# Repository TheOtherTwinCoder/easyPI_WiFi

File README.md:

# easyPI_WiFi
Simply, a devboard with a WiFi shield using the RPI RM2, made for Macondo!

*Well, what's the point?*

I made easyPI WiFi for one simple reason - its customizability! Most custom board related to the Pi Pico don't have the ability to use shields (especially due to the lack of some pins, like pins 25 and 29) - which isn't great for adding features to your board (from just the regular features of a microcontroller!) 

Features:

- EVERY GPIO pin included with the RP2040 - such as pins 25 and 29 - while not losing out on other pins, like the ADC pins!
- RPI_RM2 compatibility with the shield, allowing for WiFi and Bluetooth
- USB-C rather than the normally used Micro-USB with Picos
- 264 KB of on-chip SRAM
- Software compatible with hundreds of distros and repos (mainly due to RP2040 support)
- All the features of a regular Pi Pico, too!

## How It Works
This'll be added once I build the PCB after reciving my parts!

## BOM
| Reference / Item | Package / Description | Qty | Value / Part | Source / Link | Cost (USD) |
|------------------|----------------------|-----|--------------|---------------|------------|
| C1, C10 | 0402 | 2 | 1uF | https://jlcpcb.com/partdetail/53938-CL05A105KA5NQNC/C52923 | |
| C11, C12, C17, C2, C3, C4, C5, C6, C7, C8, C9 | 0402 | 11 | 0.1uF | https://jlcpcb.com/partdetail/1877-CL05B104KO5NNNC/C1525 | |
| C13, C14 | 0402 | 2 | 10uF | https://jlcpcb.com/partdetail/16204-CL05A106MQ5NUNC/C15525 | |
| C15, C16 | 0402 | 2 | 33pF | https://jlcpcb.com/partdetail/1914-0402CG330J500NT/C1562 | |
| J1 | USB_C_Receptacle_HRO_TYPE-C-31-M-12 | 1 | USB-C Receptacle USB2.0 14P | https://jlcpcb.com/partdetail/Korean_HropartsElec-TYPE_C_31_M12/C165948 | |
| J2, J4 | PinHeader_1x20_P2.54mm_Vertical | 2 | Conn_01x20 | https://jlcpcb.com/partdetail/51993-2_54_1_20PStraightpin/C50981 | |
| J3 | PinHeader_1x03_P2.54mm_Vertical | 1 | 1x3 Header | https://jlcpcb.com/partdetail/25717-1_27_13PPin/C24980 | |
| J5 | PinHeader_1x01_P2.54mm_Vertical | 1 | Conn_01x01 | Not on LCSC | |
| R1, R2 | 0402 | 2 | 5.1kΩ | https://jlcpcb.com/partdetail/26648-0402WGF5101TCE/C25905 | |
| R3, R4 | 0402 | 2 | 27Ω | https://jlcpcb.com/partdetail/1445-RC02K360JT/C1093 | |
| R5, R7 | 0402 | 2 | 1kΩ | https://jlcpcb.com/partdetail/12256-0402WGF1001TCE/C11702 | |
| R6 | 0402 | 1 | 10kΩ | https://jlcpcb.com/partdetail/26274-0402WGJ0103TCE/C25531 | |
| SW1 | Alps SKRK Push Button | 1 | SPST-NO Push Switch | https://www.lcsc.com/product-detail/C2837531.html | |
| U1 | QFN-56-1EP 7x7mm P0.4mm EP3.2x3.2mm | 1 | RP2040 | https://jlcpcb.com/partdetail/LumbergAutomation-2040/C18129058 | |
| U2 | SOT-23 | 1 | MCP1700 Regulator | https://jlcpcb.com/partdetail/MicrochipTech-MCP1700_3302ETO/C511277 | |
| U3 | Winbond USON-8-1EP 3x2mm P0.5mm EP0.2x1.6mm | 1 | W25Q16JVSSIQ Flash Memory | https://jlcpcb.com/partdetail/WinbondElec-W25Q16JVSSIQ/C82317 | |
| Y1 | Crystal_SMD_3225-4Pin 3.2x2.5mm | 1 | 12 MHz Crystal | https://jlcpcb.com/partdetail/NDK-NX3225GA_12MHZ_STD_CRG2/C481407 | |
| LCSC Resistors (10kΩ + 470Ω) | Purchase | 1 | Components | LCSC | 1.55 |
| LCSC Shipping | Shipping | 1 | Shipping | LCSC | 9.01 |
| LCSC Handling Fee | Fee | 1 | Handling | LCSC | 3.00 |
| Amazon Socket Headers | Purchase | 1 | Socket Headers | Amazon | 8.81 |
| PiShop RM2 Module | Purchase | 1 | RM2 Module | PiShop | 4.40 |
| PiShop Shipping | Shipping | 1 | Shipping | PiShop | 6.76 |
| JLCPCB PCBs | Fabrication | 1 | PCB Order | JLCPCB | 5.12 |
| JLCPCB Shipping | Shipping | 1 | Shipping | JLCPCB | 66.03 |
| **TOTAL** |  |  |  |  | **105.13** |

## Images
Schematic for Main PCB:

PCB for Main PCB:

3D View for Main PCB: 

Schematic for WiFi Shield:

PCB for WiFi Shield:

3D View for WiFi Shield:

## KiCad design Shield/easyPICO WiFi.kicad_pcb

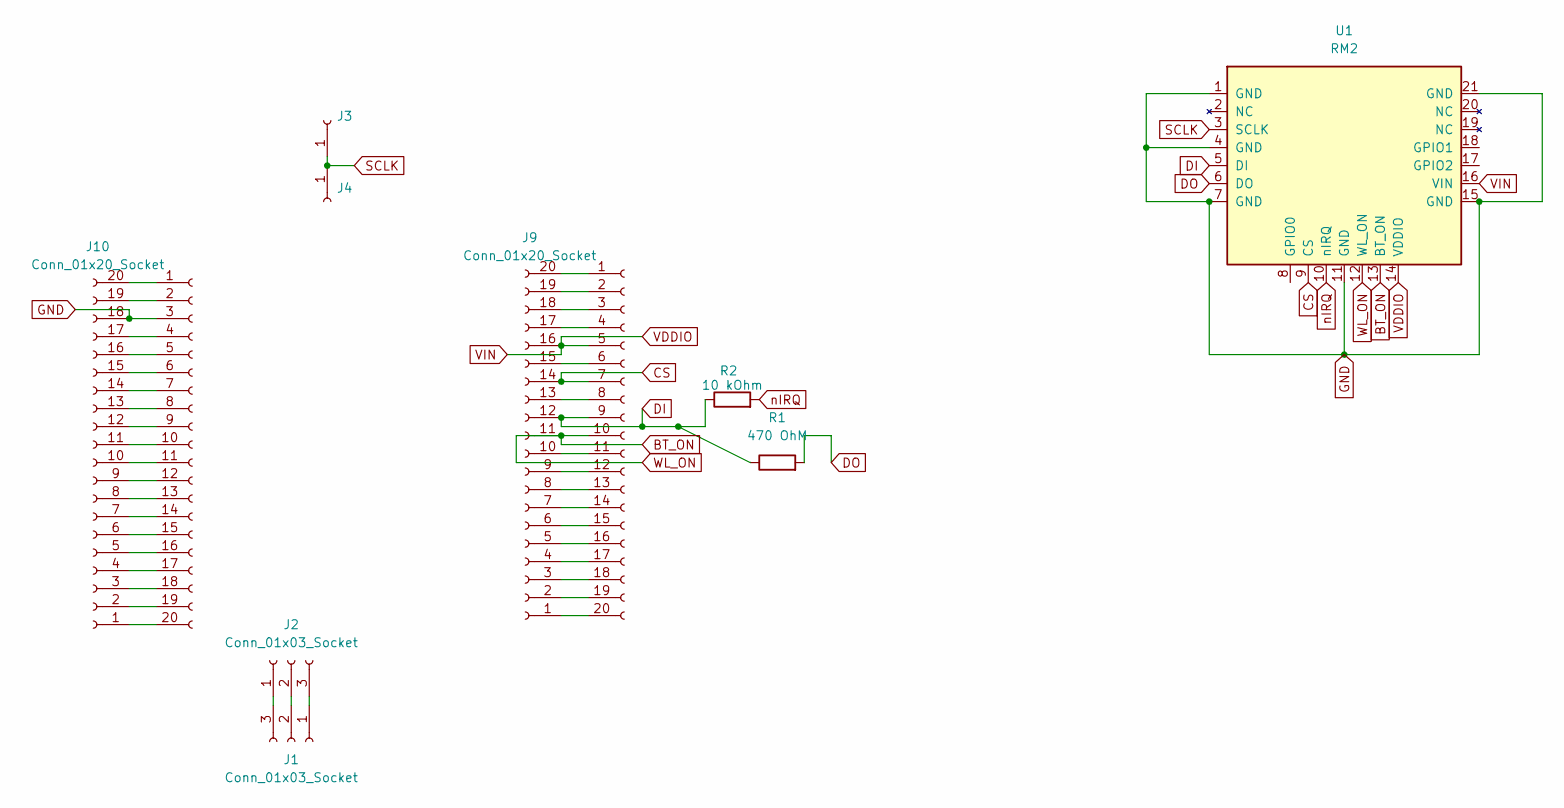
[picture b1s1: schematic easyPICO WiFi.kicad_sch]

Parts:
J1, J2: Conn_01x03_Socket; PinSocket_1x03_P2.54mm_Vertical
J3, J4: Conn_01x01_Socket; PinSocket_1x01_P2.54mm_Vertical
J8, J9, J10, J11: Conn_01x20_Socket; PinSocket_1x20_P2.54mm_Vertical
R1: 470 OhM; R_0805_2012Metric
R2: 10 kOhm; R_0805_2012Metric
U1: RM2; rpi_rmc20452t

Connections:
BT_ON: J8.10, J9.11, U1.12 (WL_ON), U1.13 (BT_ON)
CS: J8.7, J9.14, U1.9 (CS)
DI: J8.9, J9.12, R1.1, R2.1, U1.5 (DI)
DO: R1.2, U1.6 (DO)
GND: J10.18, J11.3, U1.1 (GND), U1.4 (GND), U1.7 (GND), U1.11 (GND), U1.15 (GND), U1.21 (GND)
unnamed: J1.1, J2.3
unnamed: J1.2, J2.2
unnamed: J1.3, J2.1
unnamed: J8.1, J9.20
unnamed: J8.2, J9.19
unnamed: J8.3, J9.18
unnamed: J8.4, J9.17
unnamed: J8.6, J9.15
unnamed: J8.8, J9.13
unnamed: J8.11, J9.10
unnamed: J8.12, J9.9
unnamed: J8.13, J9.8
unnamed: J8.14, J9.7
unnamed: J8.15, J9.6
unnamed: J8.16, J9.5
unnamed: J8.17, J9.4
unnamed: J8.18, J9.3
unnamed: J8.19, J9.2
unnamed: J8.20, J9.1
unnamed: J10.1, J11.20
unnamed: J10.2, J11.19
unnamed: J10.3, J11.18
unnamed: J10.4, J11.17
unnamed: J10.5, J11.16
unnamed: J10.6, J11.15
unnamed: J10.7, J11.14
unnamed: J10.8, J11.13
unnamed: J10.9, J11.12
unnamed: J10.10, J11.11
unnamed: J10.11, J11.10
unnamed: J10.12, J11.9
unnamed: J10.13, J11.8
unnamed: J10.14, J11.7
unnamed: J10.15, J11.6
unnamed: J10.16, J11.5
unnamed: J10.17, J11.4
unnamed: J10.19, J11.2
unnamed: J10.20, J11.1
SCLK: J3.1 (Pin_1_1), J4.1 (Pin_1_1), U1.3 (SCLK)
VDDIO: J8.5, J9.16, U1.14 (VDDIO), U1.16 (VIN)
nIRQ: R2.2, U1.10 (nIRQ)

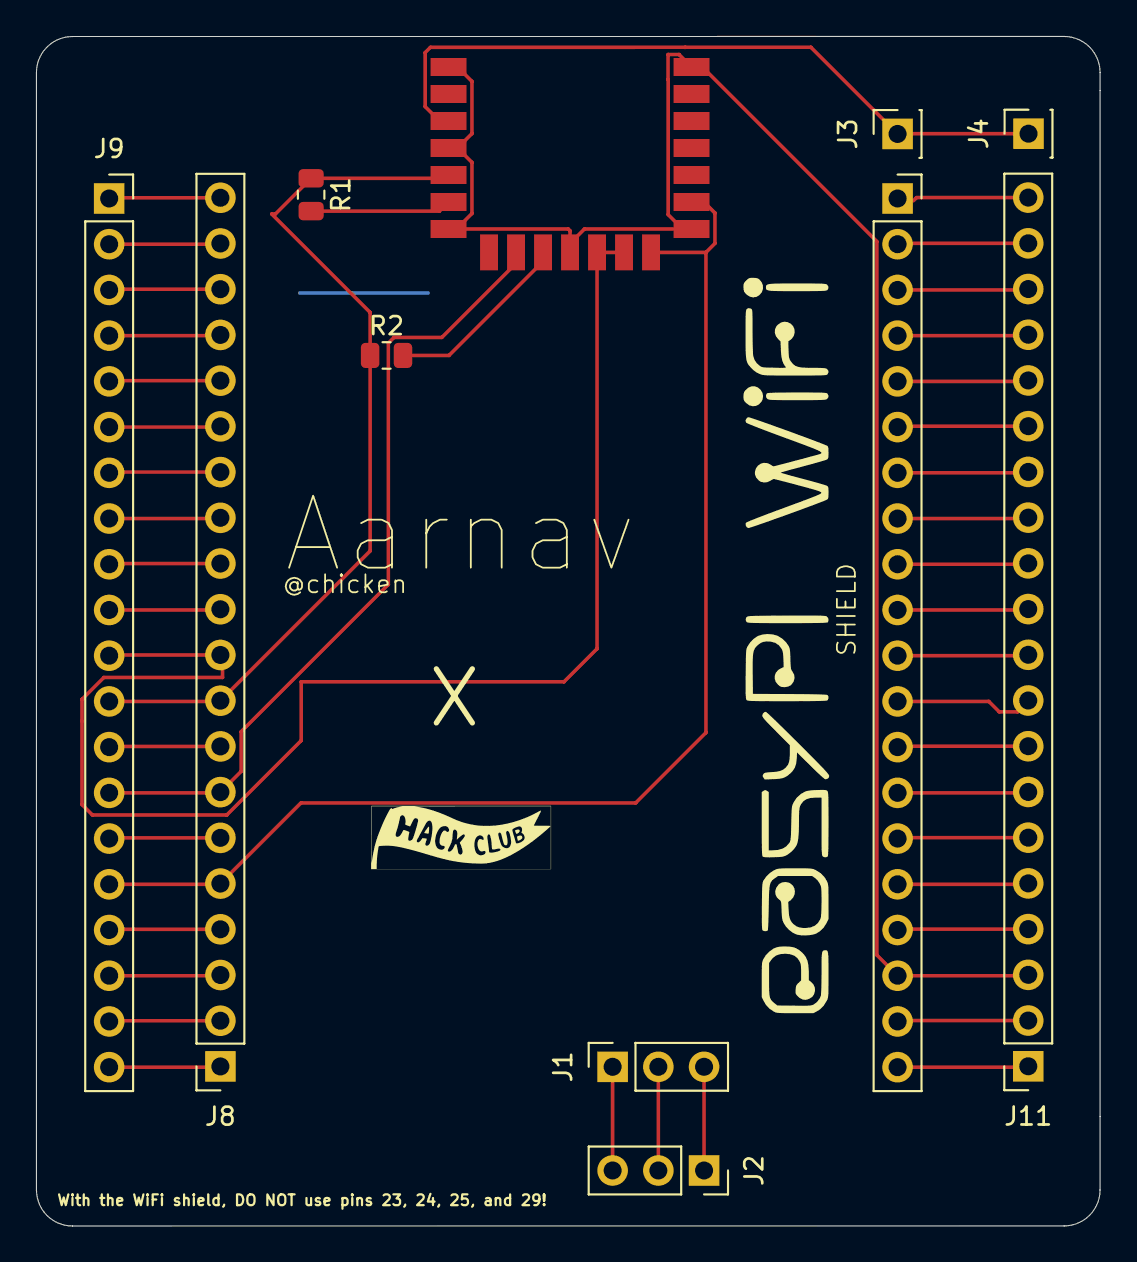
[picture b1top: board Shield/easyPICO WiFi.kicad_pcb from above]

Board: 2 copper layers, 59.1 x 66.1 mm, 11 parts (0 on the bottom side), 46 nets.

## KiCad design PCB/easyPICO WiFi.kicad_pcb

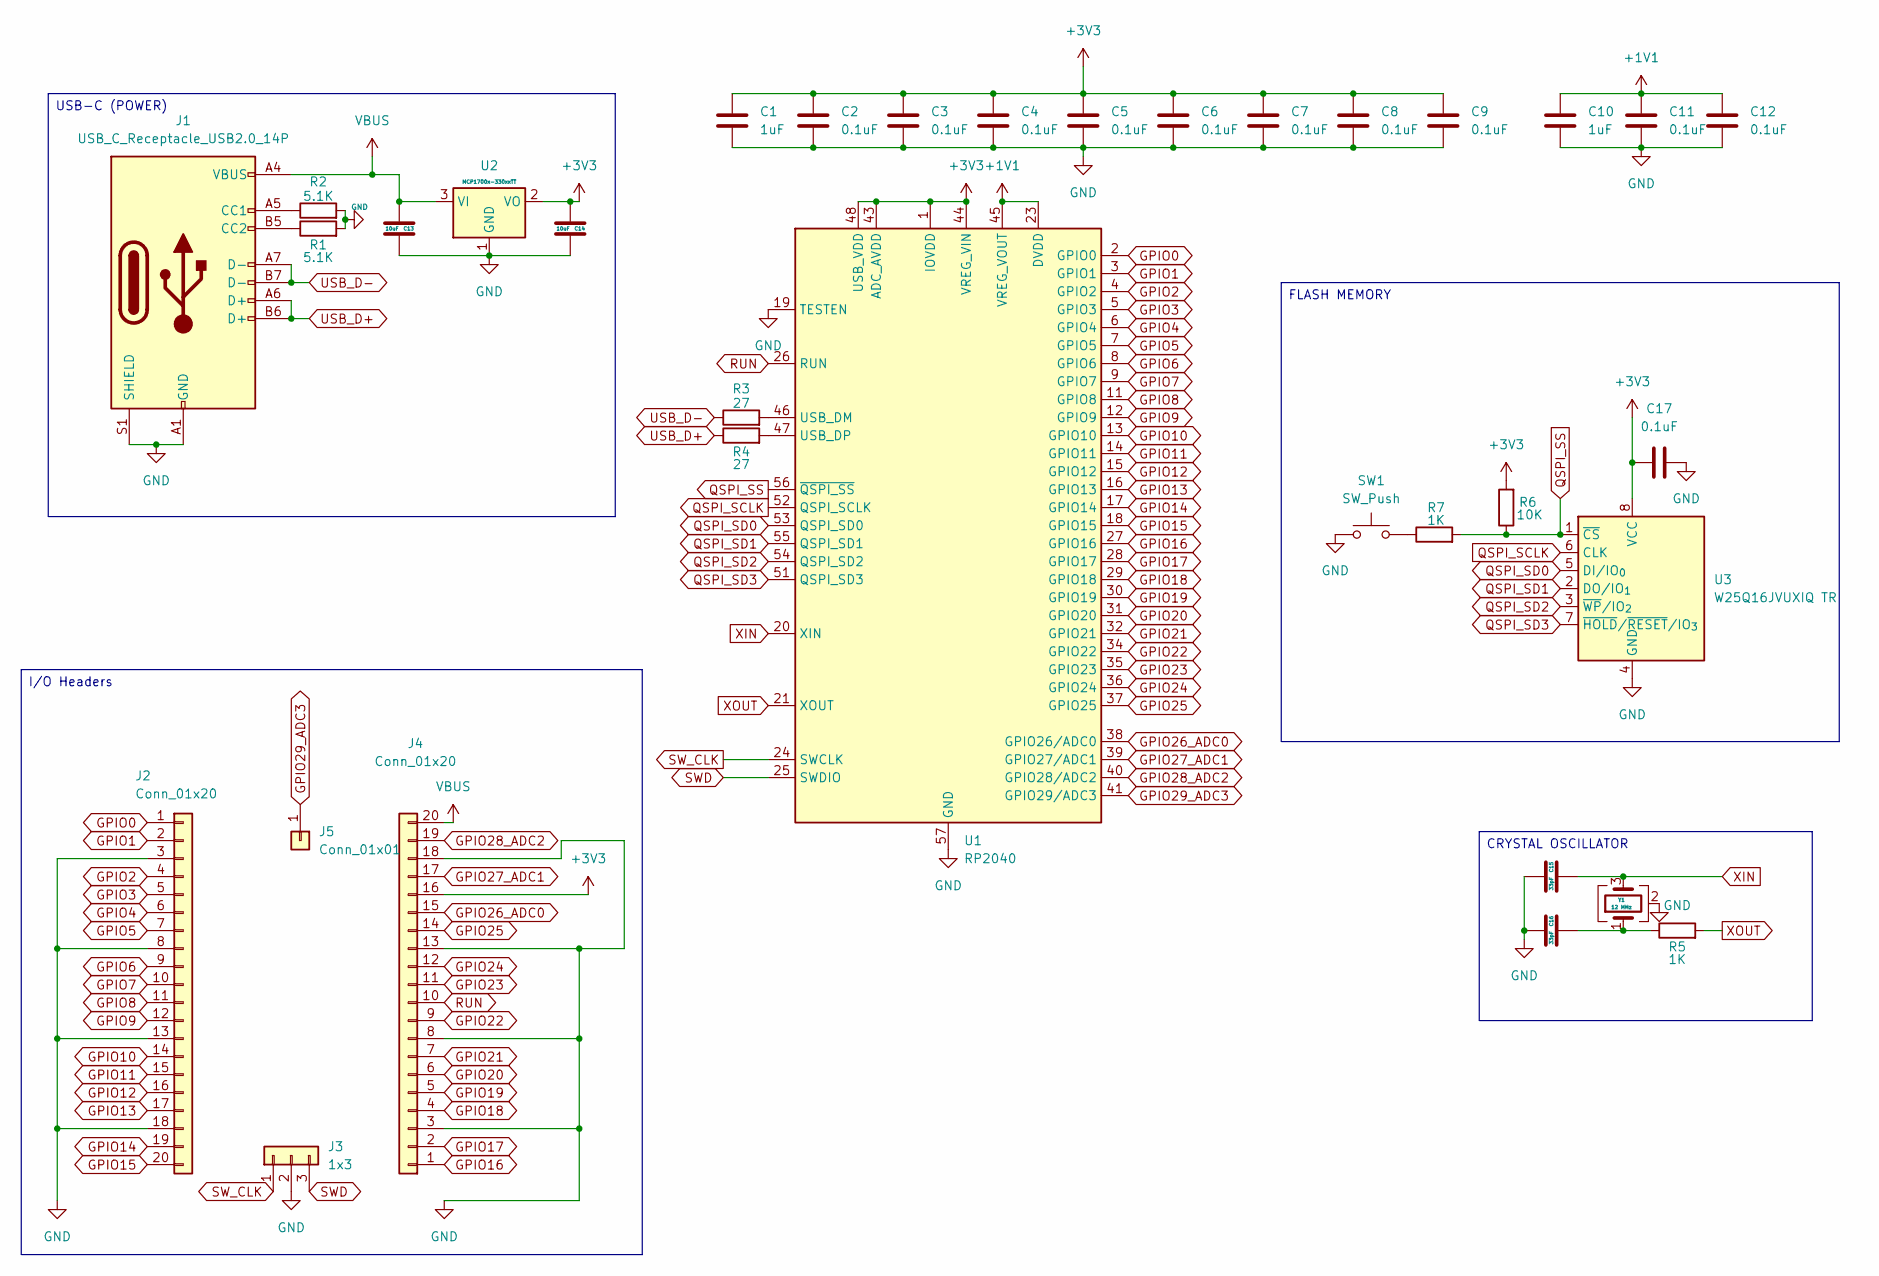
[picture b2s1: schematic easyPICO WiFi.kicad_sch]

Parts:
C1, C10: 1uF; C_0402_1005Metric
C2, C3, C4, C5, C6, C7, C8, C9, C11, C12, C17: 0.1uF; C_0402_1005Metric
C13, C14: 10uF; C_0402_1005Metric
C15, C16: 33pF; C_0402_1005Metric
J1: USB_C_Receptacle_USB2.0_14P; USB_C_Receptacle_HRO_TYPE-C-31-M-12
J2, J4: Conn_01x20; PinHeader_1x20_P2.54mm_Vertical
J3: 1x3; PinHeader_1x03_P2.54mm_Vertical
J5: Conn_01x01; PinHeader_1x01_P2.54mm_Vertical
R1, R2: 5.1K; R_0402_1005Metric
R3, R4: 27; R_0402_1005Metric
R5, R7: 1K; R_0402_1005Metric
R6: 10K; R_0402_1005Metric
SW1: SW_Push; SW_Push_SPST_NO_Alps_SKRK
U1: RP2040; QFN-56-1EP_7x7mm_P0.4mm_EP3.2x3.2mm
U2: MCP1700x-330xxTT; SOT-23
U3: W25Q16JVUXIQ TR; Winbond_USON-8-1EP_3x2mm_P0.5mm_EP0.2x1.6mm
Y1: 12 MHz; Crystal_SMD_3225-4Pin_3.2x2.5mm

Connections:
+1V1: C10.1, C11.1, C12.1, U1.23 (DVDD), U1.45 (VREG_VOUT), U1.50 (DVDD)
+3V3: C1.1, C2.1, C3.1, C4.1, C5.1, C6.1, C7.1, C8.1, C9.1, C14.1, C17.1, J4.16, R6.2, U1.1 (IOVDD), U1.10 (IOVDD), U1.22 (IOVDD), U1.33 (IOVDD), U1.42 (IOVDD), U1.43 (ADC_AVDD), U1.44 (VREG_VIN), U1.48 (USB_VDD), U1.49 (IOVDD), U2.2 (VO), U3.8 (VCC)
GND: C1.2, C2.2, C3.2, C4.2, C5.2, C6.2, C7.2, C8.2, C9.2, C10.2, C11.2, C12.2, C13.2, C14.2, C15.1, C16.1, C17.2, J1.A1 (GND), J1.A12 (GND), J1.B1 (GND), J1.B12 (GND), J1.S1 (SHIELD), J2.3, J2.8, J2.13, J2.18, J3.2, J4.3, J4.8, J4.13, J4.18, R1.2, R2.2, SW1.1, U1.19 (TESTEN), U1.57 (GND), U2.1 (GND), U3.4 (GND), Y1.2 (G), Y1.4 (G)
GPIO0: J2.1, U1.2 (GPIO0)
GPIO1: J2.2, U1.3 (GPIO1)
GPIO2: J2.4, U1.4 (GPIO2)
GPIO3: J2.5, U1.5 (GPIO3)
GPIO4: J2.6, U1.6 (GPIO4)
GPIO5: J2.7, U1.7 (GPIO5)
GPIO6: J2.9, U1.8 (GPIO6)
GPIO7: J2.10, U1.9 (GPIO7)
GPIO8: J2.11, U1.11 (GPIO8)
GPIO9: J2.12, U1.12 (GPIO9)
GPIO10: J2.14, U1.13 (GPIO10)
GPIO11: J2.15, U1.14 (GPIO11)
GPIO12: J2.16, U1.15 (GPIO12)
GPIO13: J2.17, U1.16 (GPIO13)
GPIO14: J2.19, U1.17 (GPIO14)
GPIO15: J2.20, U1.18 (GPIO15)
GPIO16: J4.1, U1.27 (GPIO16)
GPIO17: J4.2, U1.28 (GPIO17)
GPIO18: J4.4, U1.29 (GPIO18)
GPIO19: J4.5, U1.30 (GPIO19)
GPIO20: J4.6, U1.31 (GPIO20)
GPIO21: J4.7, U1.32 (GPIO21)
GPIO22: J4.9, U1.34 (GPIO22)
GPIO23: J4.11, U1.35 (GPIO23)
GPIO24: J4.12, U1.36 (GPIO24)
GPIO25: J4.14, U1.37 (GPIO25)
GPIO26_ADC0: J4.15, U1.38 (GPIO26/ADC0)
GPIO27_ADC1: J4.17, U1.39 (GPIO27/ADC1)
GPIO28_ADC2: J4.19, U1.40 (GPIO28/ADC2)
GPIO29_ADC3: J5.1, U1.41 (GPIO29/ADC3)
unnamed: C16.2, R5.1, Y1.1
unnamed: J1.A5 (CC1), R2.1
unnamed: J1.B5 (CC2), R1.1
unnamed: R7.1, SW1.2
unnamed: R3.2, U1.46 (USB_DM)
unnamed: R4.2, U1.47 (USB_DP)
QSPI_SCLK: U1.52 (QSPI_SCLK), U3.6 (CLK)
QSPI_SD0: U1.53 (QSPI_SD0), U3.5 (DI/IO_{0})
QSPI_SD1: U1.55 (QSPI_SD1), U3.2 (DO/IO_{1})
QSPI_SD2: U1.54 (QSPI_SD2), U3.3 (~WP/IO_{2})
QSPI_SD3: U1.51 (QSPI_SD3), U3.7 (~HOLD/~RESET/IO_{3})
QSPI_SS: R6.1, R7.2, U1.56 (~QSPI_SS), U3.1 (~CS)
RUN: J4.10, U1.26 (RUN)
SWD: J3.3, U1.25 (SWDIO)
SW_CLK: J3.1, U1.24 (SWCLK)
USB_D+: J1.A6 (D+), J1.B6 (D+), R4.1
USB_D-: J1.A7 (D-), J1.B7 (D-), R3.1
VBUS: C13.1, J1.A4 (VBUS), J1.A9 (VBUS), J1.B4 (VBUS), J1.B9 (VBUS), J4.20, U2.3 (VI)
XIN: C15.2, U1.20 (XIN), Y1.3
XOUT: R5.2, U1.21 (XOUT)

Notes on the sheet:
CRYSTAL OSCILLATOR
FLASH MEMORY
USB-C (POWER)
I/O Headers

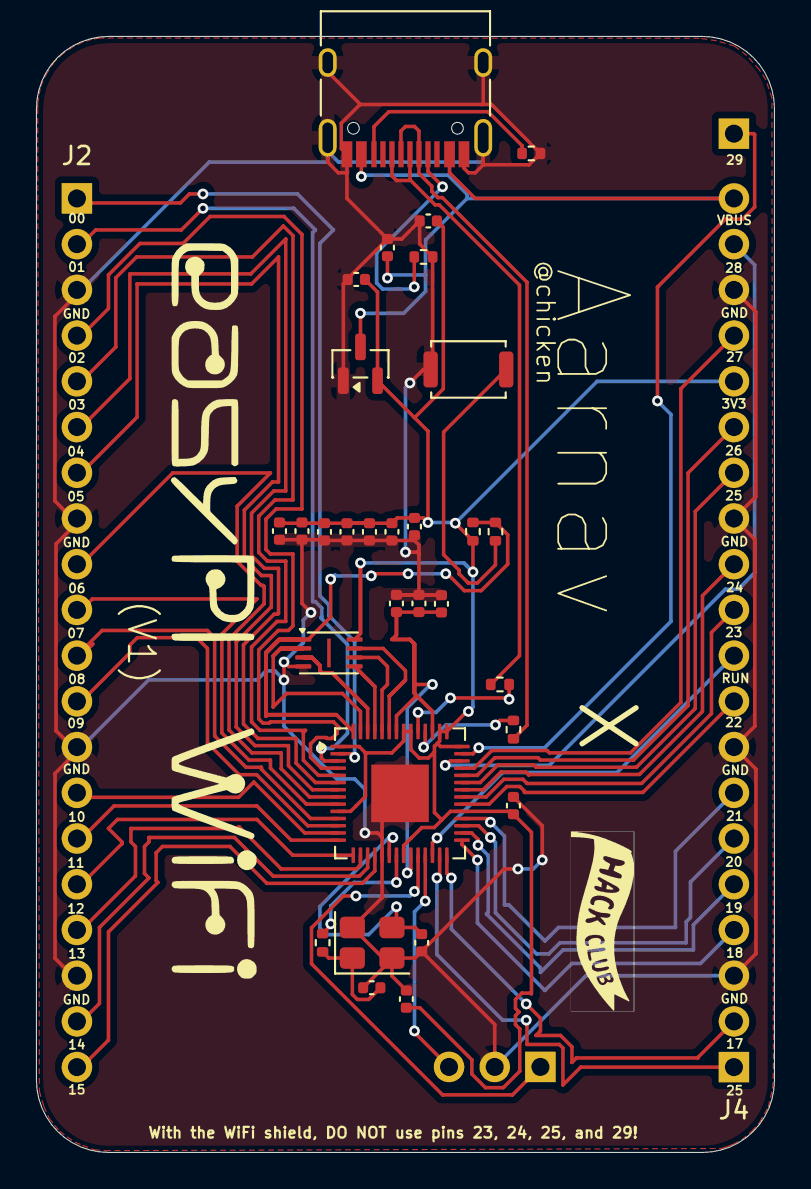
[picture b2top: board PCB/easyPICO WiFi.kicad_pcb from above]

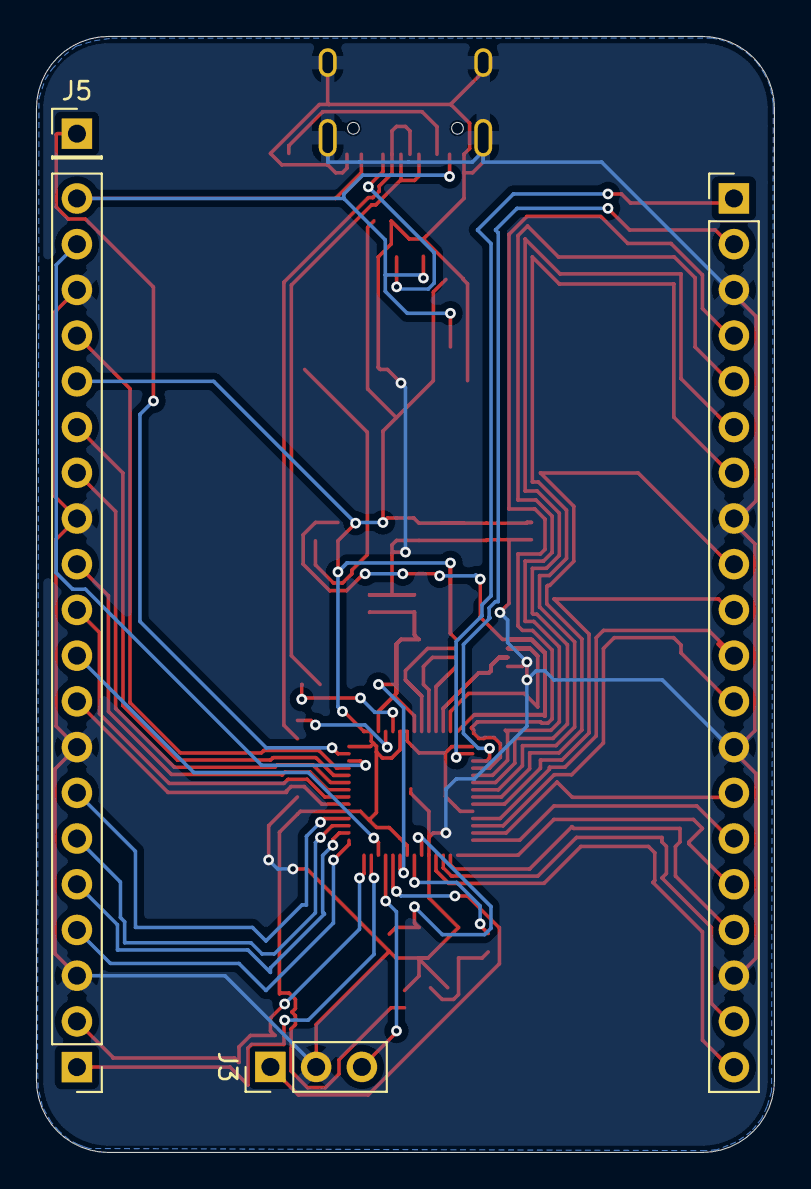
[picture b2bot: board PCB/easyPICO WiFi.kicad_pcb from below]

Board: 2 copper layers, 41.0 x 62.0 mm, 34 parts (4 on the bottom side), 53 nets.

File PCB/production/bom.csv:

Designator,Footprint,Quantity,Value,LCSC Part #
"C1, C10",0402,2,1uF,
"C11, C12, C17, C2, C3, C4, C5, C6, C7, C8, C9",0402,11,0.1uF,
"C13, C14",0402,2,10uF,
"C15, C16",0402,2,33pF,
J1,USB_C_Receptacle_HRO_TYPE-C-31-M-12,1,USB_C_Receptacle_USB2.0_14P,
"J2, J4",PinHeader_1x20_P2.54mm_Vertical,2,Conn_01x20,
J3,PinHeader_1x03_P2.54mm_Vertical,1,1x3,
J5,PinHeader_1x01_P2.54mm_Vertical,1,Conn_01x01,
"R1, R2",0402,2,5.1K,
"R3, R4",0402,2,27,
"R5, R7",0402,2,1K,
R6,0402,1,10K,
SW1,SW_Push_SPST_NO_Alps_SKRK,1,SW_Push,
U1,QFN-56-1EP_7x7mm_P0.4mm_EP3.2x3.2mm,1,2040,
U2,SOT-23,1,MCP,
U3,Winbond_USON-8-1EP_3x2mm_P0.5mm_EP0.2x1.6mm,1,Mem,
Y1,Crystal_SMD_3225-4Pin_3.2x2.5mm,1,12 MHz,

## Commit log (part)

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2026-06-22 Create test
2026-06-24 add files
2026-06-26 Add Updated Files
2026-06-27 gerbers
2026-06-27 Create cadfiles
